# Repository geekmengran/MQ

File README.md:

### MangoPi Nezha-MQ

### Introduction

This micro development board is specially designed to run Linux. Despite a mini body, it has all the vital functions. Equipped with D1s(RISC-V core) as the maincontroller chip, the board offers various commonly-used peripheral ports: GPIO, I2C & SPI, SDIO, Audio port(record, play), Video(RGB666 Display, touch, DVP, DSI and LVDS), USB Host, OTG, etc. Besides, the board comes with a built-in 64MB DDR and onboard WiFi, which fully supports Linux ecology and running complete Python.

### Spectification
  * D1s with 64MB DDR, RISC-V core up to 1GHz
  * Type-C USB-OTG and HOST
  * 22Pin expand x2(all pins out)
  * TF card
  * RTL8189F WiFi or other WiFi/BT module
  * FPC connector 15Pins DSI, 40Pins RGB, 24Pins DVP/RMII, 6Pins CTP
  * MIC and Audio OUT
  * Fel,reset button
  * 4x4cm size

### PCB

### SCH

### V1.6 Mass-Production

### MQ on the web
  * [mass-production on twitter]( https://twitter.com/mangopi_sbc/status/1469197984303022080)
  * [A shell](https://twitter.com/mangopi_sbc/status/1472535322605273090)
  * [MoeOS on MQ](https://www.lirui.tech/post/2021/12/MoeOS%E6%90%AC%E5%AE%B6%E5%88%B0Nezha-MQ%E4%B8%8A%E5%95%A6%EF%BC%88D1s%E8%A3%B8%E6%9C%BA%E7%A8%8B%E5%BA%8F%E6%89%A7%E8%A1%8C%EF%BC%89.html)
  * [Getting started on MQ with Tina-Linux](https://whycan.com/t_7575.html)
  * [use MQ drive RGB display](https://blog.csdn.net/qq_34440409/article/details/122021748)
  * [MQ first experience](https://www.neko.ooo/mongopi-mq1-hands-on/)
  * [RT-Thread on MQ](https://bbs.aw-ol.com/topic/908/)
  * [MQ's MIPI-DSI](https://bbs.aw-ol.com/topic/808/)
  * [more on Twitter](https://twitter.com/search?q=mangopi)

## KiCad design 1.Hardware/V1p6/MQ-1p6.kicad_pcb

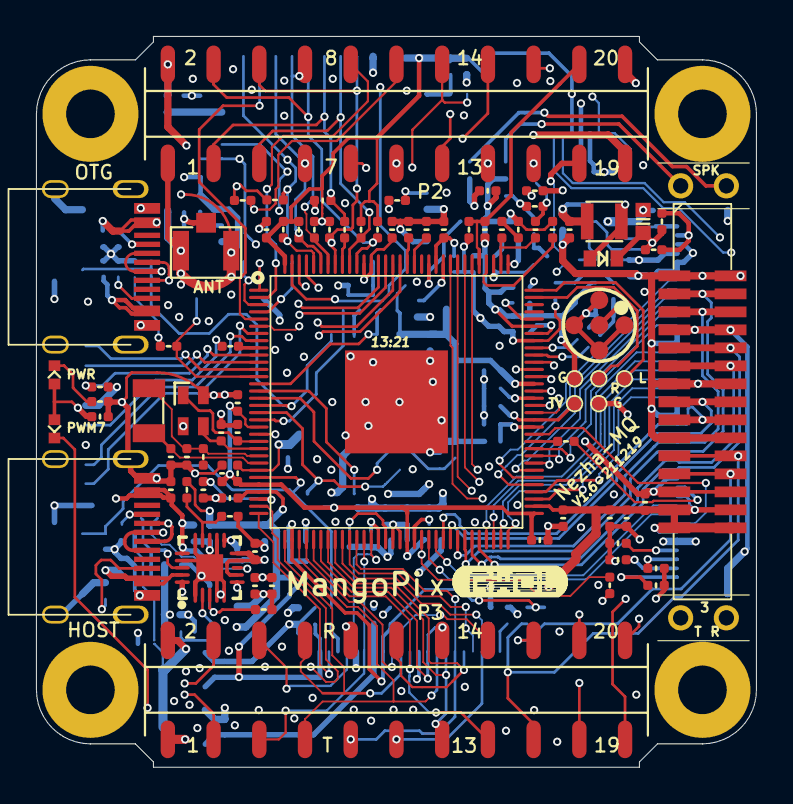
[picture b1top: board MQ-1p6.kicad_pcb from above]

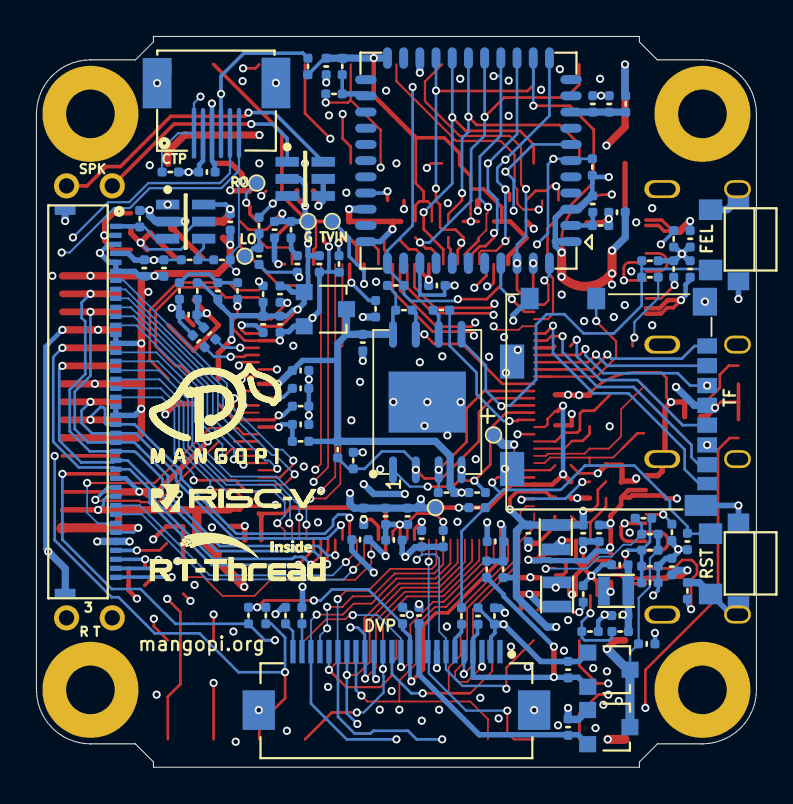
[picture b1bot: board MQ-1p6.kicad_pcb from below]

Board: 4 copper layers, 40.0 x 40.6 mm, 204 parts (120 on the bottom side), 160 nets.

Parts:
C1: 1uF 50V; C0603
C2, C3, C10, C14, C15, C21, C23, C25, C26, C27, C28, C30, C32, C54, C55, C60, C64, C65, C67, C76, C81, C82, C83, C85: 10uF; C0402
C4, C5, C6, C12, C13, C16, C20, C29, C31, C33, C34, C35, C36, C37, C38, C39, C41, C42, C46, C47, C51, C52, C53, C59, C61, C62, C63, C66, C70, C77, C79, C80, C84, C86: 0.1uF; C0402
C7: 100pF; C0402
C8, C9, C43, C45: 22pF; C0402
C11, C22, C44, C50, C68: 2.2uF; C0402
C18, C48, C58: NC; C0402
C19, C24, C69, C71: 1uF; C0402
C40, C78: 0.47uF; C0402
C49, C72, C73, C74, C75: 1nF; C0402
D1: MSK4010; SOD523
DS1: GREEN; LED0402
DS2: BLUE; LED0402
J1: TF5033981892; TFCARD-1040310811
J2, J3: USB-TypeC-16P; USB-TYPEC-16P
J4: ipex; I-PEX SOCKET
L1, L2, L3: 2.2uH; VLS2016
L4: 10uH; VLS252010
M1: MIC; MIC-T
P1: FFC40-RGBLCD; FFC{slash}SM0.5-1H40
P2: Header 11X2; _×ÊÁÏ¿â_ADLIB_A.PcbLib_HDR2X11T
P3: Header 11X2; _ÏîÄ¿_ADLIB_A.Pc_HDR2X11T
P4: FPC6
P5: Header15-MIPI; MIPI_CSI_1.0_30PIN
P6, P8: Header 2; HDR1X2-XIAO
R1, R2, R5, R23, R29, R37: 100K; R0402
R3, R39, R43, R49, R59, R64: 33R; R0402
R4, R19: 2R7; R0402
R6, R24, R26, R28, R30, R36, R80: 5.1K; R0402
R7, R18, R25, R33, R48, R72, R73, R74, R75, R78, R81, R82: 10K; R0402
R8, R40: 680K 1%; R0402
R9, R11, R13, R20, R21: 150K 1%; R0402
R10: 300K 1%; R0402
R12: 75K 1%; R0402
R14, R46, R70: NC/100K; R0402
R15, R38, R53, R56, R58, R61, R71, R79: 0R; R0402
R16, R17, R55, R60: 75R; R0402
R27, R34: 1K; R0402
R32, R35, R45, R50, R52, R57, R76, R77, R84: NC; R0402
R41: NC/0R; R0402
R42: 240R 1%; R0402
R47, R65, R66, R67, R68, R69: 47K; R0402
R54: NC/1K; R0402
S1, S2: SW-CE; MINISW
TP1, TP2, TP3, TP4, TP5, TP6, TP7, TP8, TP9, TP10, TP11: TEST POINT; TEST-POINT
U1: D1s-eLQFP128; QFP129P40B1600_1600H160
U2: XC6206-1.8V; SOT23
U3: SPIFLASH_SOP8W; WSON-SPIFLASH
U4: RY1303; QFN40P300X300X80_HS-21N
U5: MT9284-28J; SOT23-6
U6: WIFI; _×ÊÁÏ¿â_ADLIB_A.PcbLib_AP6212
U7: OV-DVP; FFC{slash}SM0.5-2H24-OV5640
U8: XC6206-1.2; SOT23
U9: XC6206-2.8; SOT23
U10: PAM8301; SOT23-6
X1: XTAL2520-24M CL=18PF; XTAL2520
XT1: 32.768K CL=12.5pF; Y3215

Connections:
32I: C45.1, R40.2, U1.25, XT1.1
32O: C43.1, R40.1, U1.24, XT1.2
AAGND: C61.1, C63.1, C64.2, R53.1, U7.2, U9.1
AGND: C5.1, C11.2, C22.1, C40.1, C49.1, C78.2, C81.2, C85.2, C86.1, R3.2, R15.2, R34.2, R64.2, TP7.1, TP10.1, U1.91, U2.1, U10.2
AP-CLK24M-OUT: R41.1, U1.21
AP_WAKE_BT: P2.16, R46.1, U1.125, U6.6
AVCC1.8: C5.2, C11.1, C22.2, R29.2, R55.1, R71.2, U1.89, U1.97, U2.2
AVDD2V8: C63.2, C64.1, R56.2, U7.4, U9.2
BT_EN: P2.18, R37.2, U1.127, U6.34
BT_WAKE_AP: P2.17, U1.126, U6.7
CK_N: P1.28, P5.5, U1.60
CK_P: P1.27, P5.6, U1.59
CTP_INT: P3.20, P4.4, R82.1, U1.85
CTP_RST: P3.19, P4.1, R81.1, U1.86
D0_N: P1.24, P5.8, U1.56
D0_P: P1.23, P5.9, U1.55
D1_N: P1.26, P5.2, U1.58
D1_P: P1.25, P5.3, U1.57
DVP-Y2: P3.9, U1.43, U7.19
DVP-Y3: P3.10, U1.42, U7.21
DVP-Y4: P3.11, U1.41, U7.22
DVP-Y5: P3.12, U1.40, U7.20
DVP-Y6: P3.13, U1.39, U7.18
DVP-Y7: P3.14, U1.38, U7.16
DVP-Y8: P3.15, U1.37, U7.14
DVP-Y9: P3.16, U1.36, U7.12
DVP_DVDD: C62.2, C67.1, U7.10, U8.2
DVP_HSYNC: P3.5, U1.44, U7.9
DVP_PCLK: P3.7, U1.35, U7.17
DVP_RST: R52.1, U7.6
DVP_SCL: P3.17, P4.6, P5.11, R72.1, U1.32, U7.5
DVP_SDA: P3.18, P4.5, P5.12, R73.1, U1.31, U7.3
DVP_VSYNC: P3.6, U1.45, U7.7
DVP_XCLK: P3.8, U1.33, U7.13
GND: C1.2, C2.1, C3.2, C4.1, C8.2, C9.2, C10.1, C12.1, C13.1, C14.1, C16.1, C18.1, C19.1, C20.1, C21.1, C23.2, C24.1, C25.2, C26.2, C27.2, C28.2, C29.1, C30.2, C31.1, C32.2, C33.1, C34.1, C35.1, C36.1, C37.1, C38.1, C39.1, C41.2, C42.1, C43.2, C44.2, C45.2, C48.1, C50.2, C51.1, C52.1, C53.1, C55.1, C58.1, C59.2, C60.1, C62.1, C65.2, C66.1, C67.2, C68.2, C69.2, C70.2, C71.2, C72.2, C73.2, C74.2, C75.2, C76.2, C77.1, C79.2, C82.2, C83.2, C84.2, J1.6, J1.G1, J1.G2, J1.G3, J1.G4, J1.G5, J2.0, J2.A1, J2.A12, J2.B1, J2.B12, J3.0, J3.A1, J3.A12, J3.B1, J3.B12, J4.2, J4.3, P1.3, P1.5, P1.6, P1.13, P1.14, P1.21, P1.22, P1.29, P1.36, P1.G, P2.1, P2.22, P3.1, P4.0, P4.3, P5.1, P5.4, P5.7, P5.10, P5.13, R2.2, R4.1, R6.2, R9.2, R11.2, R13.2, R14.1, R15.1, R24.2, R26.2, R28.2, R30.2, R35.2, R42.1, R46.2, R53.2, R54.2, R60.1, R70.1, R76.2, R78.2, S1.0, S1.1, S2.0, S2.2, TP2.1, TP4.1, U1.129, U3.4, U4.1, U4.4, U4.5, U4.12, U4.13, U4.15, U4.17, U4.21, U5.2, U6.1, U6.3, U6.20, U6.31, U6.33, U6.36, U7.8, U7.15, U7.P0, U8.1, X1.2, X1.4
GPADC0: C49.2, P2.20, R29.1, U1.101
HPOUTFB: C86.2, U1.100
HPOUTL: C54.1, C80.1, U1.99
HPOUTR: C6.1, C15.1, U1.98
LCD_CLK: P1.30, R59.2
LCD_D10: P1.15, U1.61
LCD_D11: P1.16, U1.62
LCD_D12: P1.17, U1.63
LCD_D13: P1.18, U1.64
LCD_D14: P1.19, U1.67
LCD_D15: P1.20, U1.68
LCD_D18: P1.7, U1.70
LCD_D19: P1.8, U1.69
LCD_D20: P1.9, U1.71
LCD_D21: P1.10, U1.72
LCD_D22: P1.11, U1.73
LCD_D23: P1.12, U1.74
LCD_DE: P1.34, U1.76
LCD_HSYNC: P1.32, U1.54
LCD_PWM: R32.2, R36.2, U5.4
LCD_VSYNC: P1.33, U1.53
LDOA-OUT: C13.2, C44.1, C77.2, C79.1, R61.2, R74.1, U1.20, U1.28, U1.50, U1.65
LEDA: C1.1, D1.K, R16.2, R17.2, U5.5
LEDK: P1.1, R4.2, U5.3
LINEINL: TP5.1, U1.96
LINEINR: TP6.1, U1.95
MICIN3N: C47.2, U1.88
MICIN3P: C46.2, U1.87
NetC4_2: C4.2, R1.2, R2.1, R45.2, U4.18
NetC6_2: C6.2, R3.1
NetC7_1: C7.1, C46.1, M1.1, R27.2
NetC7_2: C7.2, C47.1, M1.2, R34.1
NetC12_2: C12.2, R79.1, U1.77
NetC15_2: C15.2, R21.2, TP9.1
NetC40_2: C40.2, U1.92
NetC48_2: C48.2, J4.1, R38.2
NetC50_1: C50.1, U1.30
NetC54_2: C54.2, R20.2, TP8.1
NetC58_2: C58.2, R38.1, U6.2
NetC70_1: C70.1, R71.1, U1.107
NetC78_1: C78.1, U1.90
NetC80_2: C80.2, R64.1
NetC81_1: C81.1, R27.1, R55.2
NetC85_1: C85.1, R19.2, U10.4, U10.5
NetD1_A: D1.A, L4.2, U5.1
NetDS1_K: DS1.K, R6.1
NetDS2_K: DS2.K, R80.1
NetJ2_A5: J2.A5, R24.1
NetJ2_B5: J2.B5, R26.1
NetJ3_A5: J3.A5, R28.1
NetJ3_B5: J3.B5, R30.1
NetL1_1: L1.1, U4.11
NetL2_1: L2.1, U4.20
NetL3_1: L3.1, U4.6
NetP1_2: P1.2, R16.1, R17.1
NetP6_1: P6.1, U10.1
NetP6_2: P6.2, U10.6
NetR8_2: R8.2, R9.1, U4.14
NetR10_2: R10.2, R11.1, U4.3
NetR12_2: R12.2, R13.1, U4.2
NetR20_1: R20.1, R21.1, U10.3
NetR23_2: R23.2, R45.1, U4.8
NetR35_1: R35.1, U7.24
NetR39_1: R39.1, U1.120
NetR41_2: R41.2, U6.30
NetR42_2: R42.2, U1.47
NetR43_2: R43.2, U1.9
NetR47_1: R47.1, R84.2, U6.24
NetR49_1: R49.1, U1.19
NetR50_1: R50.1, U7.23
NetR54_1: R54.1, U1.106
NetR59_1: R59.1, U1.75
PB4: P3.21, U1.84
PB5: P3.22, U1.82
PB6: P8.1, U1.80
PB7: P8.2, U1.79
PD22: P2.19, R32.1, R80.2, U1.52
PG0_SDC1_CLK: C18.2, P2.3, R39.2, U6.17
PG1_SDC1_CMD: P2.4, R67.2, U1.118, U6.16
PG2_SDC1_D0: P2.5, R68.2, U1.119, U6.18
PG3_SDC1_D1: P2.6, R69.2, U1.121, U6.19
PG4_SDC1_D2: P2.7, R65.2, U1.123, U6.14
PG5_SDC1_D3: P2.8, R66.2, U1.122, U6.15
PG11: P2.14, R84.1, U1.6
RESET: C84.1, R52.2, R74.2, S2.1, U1.27
SDC0_CLK: J1.5, R43.1
SDC0_CMD: J1.3, R18.2, U1.10
SDC0_D0: J1.7, U1.8
SDC0_D1: J1.8, U1.7
SDC0_D2: J1.1, U1.12
SDC0_D3: J1.2, U1.11
SDC0_DET: J1.G6, R48.1, U1.13
SPI0_CLK: R49.2, U3.6
SPI0_CS: R7.1, U1.18, U3.1
SPI0_HOLD: R25.2, U1.14, U3.7
SPI0_MISO: R75.2, R76.1, U1.16, U3.2
SPI0_MOSI: R77.2, R78.1, S1.2, U1.17, U3.5
SPI0_WP: R33.1, U1.15, U3.3
TP-X1: C75.1, P1.37, U1.102
TP-X2: C74.1, P1.39, U1.103
TP-Y1: C73.1, P1.38, U1.104
TP-Y2: C72.1, P1.40, U1.105
TVIN0: TP11.1, U1.108
TVIN_VRN: C71.1, U1.111
TVIN_VRP: C69.1, U1.110
TV_OUT: R60.2, TP1.1, U1.78
UART1_CTS: P2.12, R70.2, U1.4, U6.41
UART1_RTS: P2.11, U1.3, U6.44
UART1_RX: P2.10, U1.2, U6.42
UART1_TX: P2.9, U1.1, U6.43
USB0_N: J3.A7, J3.B7, U1.114
USB0_P: J3.A6, J3.B6, U1.115
USB1_N: J2.A7, J2.B7, P3.3, U1.113
USB1_P: J2.A6, J2.B6, P3.4, U1.112
VCC3V3: C2.2, C3.1, C19.2, C20.2, C28.1, C29.2, C34.2, C35.2, C36.2, C41.1, C42.2, C51.2, C59.1, C60.2, C65.1, C68.1, DS1.A, DS2.A, J1.4, L1.2, P1.4, P1.31, P1.35, P2.2, P3.2, P4.2, P5.14, P5.15, R1.1, R5.1, R7.2, R8.1, R18.1, R23.1, R25.1, R33.2, R36.1, R37.1, R47.2, R48.2, R50.2, R57.1, R58.2, R65.1, R66.1, R67.1, R68.1, R69.1, R75.1, R77.1, R79.2, R81.2, R82.2, U1.29, U1.66, U1.83, U1.128, U2.3, U3.8, U6.22, U8.3, U9.3
VCC-CORE: C10.2, C32.1, C33.2, C37.2, C38.2, C39.2, C53.2, L2.2, R12.1, U1.46, U1.51, U1.81, U1.116, U1.117
VCC-DRAM: C21.2, C24.2, C30.1, C31.2, C52.2, L3.2, R10.1, U1.48, U1.49
VCC-RMII-CSI: C61.2, C66.2, R56.1, R57.2, R72.2, R73.2, U1.34, U7.11
VCCIN: C23.1, C25.1, C26.1, C27.1, C55.2, C76.1, C82.1, C83.1, J2.A4, J2.A9, J2.B4, J2.B9, J3.A4, J3.A9, J3.B4, J3.B9, L4.1, P2.21, R19.1, U4.7, U4.9, U4.10, U4.16, U4.19, U5.6
VCC_RTC: R61.1, TP3.1, U1.26
VCC_WIFI: C14.2, C16.2, R58.1, U6.9
WL_REG_ON: P2.15, R5.2, R14.2, U1.124, U6.12
WL_WAKE_AP: P2.13, U1.5, U6.13
XI: C9.1, U1.23, X1.3
XO: C8.1, U1.22, X1.1

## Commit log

2022-01-29 add a unofficial firmware
2022-01-30 update the dev pdf
2022-01-31 add T113 brief
2022-02-02 add some picture
